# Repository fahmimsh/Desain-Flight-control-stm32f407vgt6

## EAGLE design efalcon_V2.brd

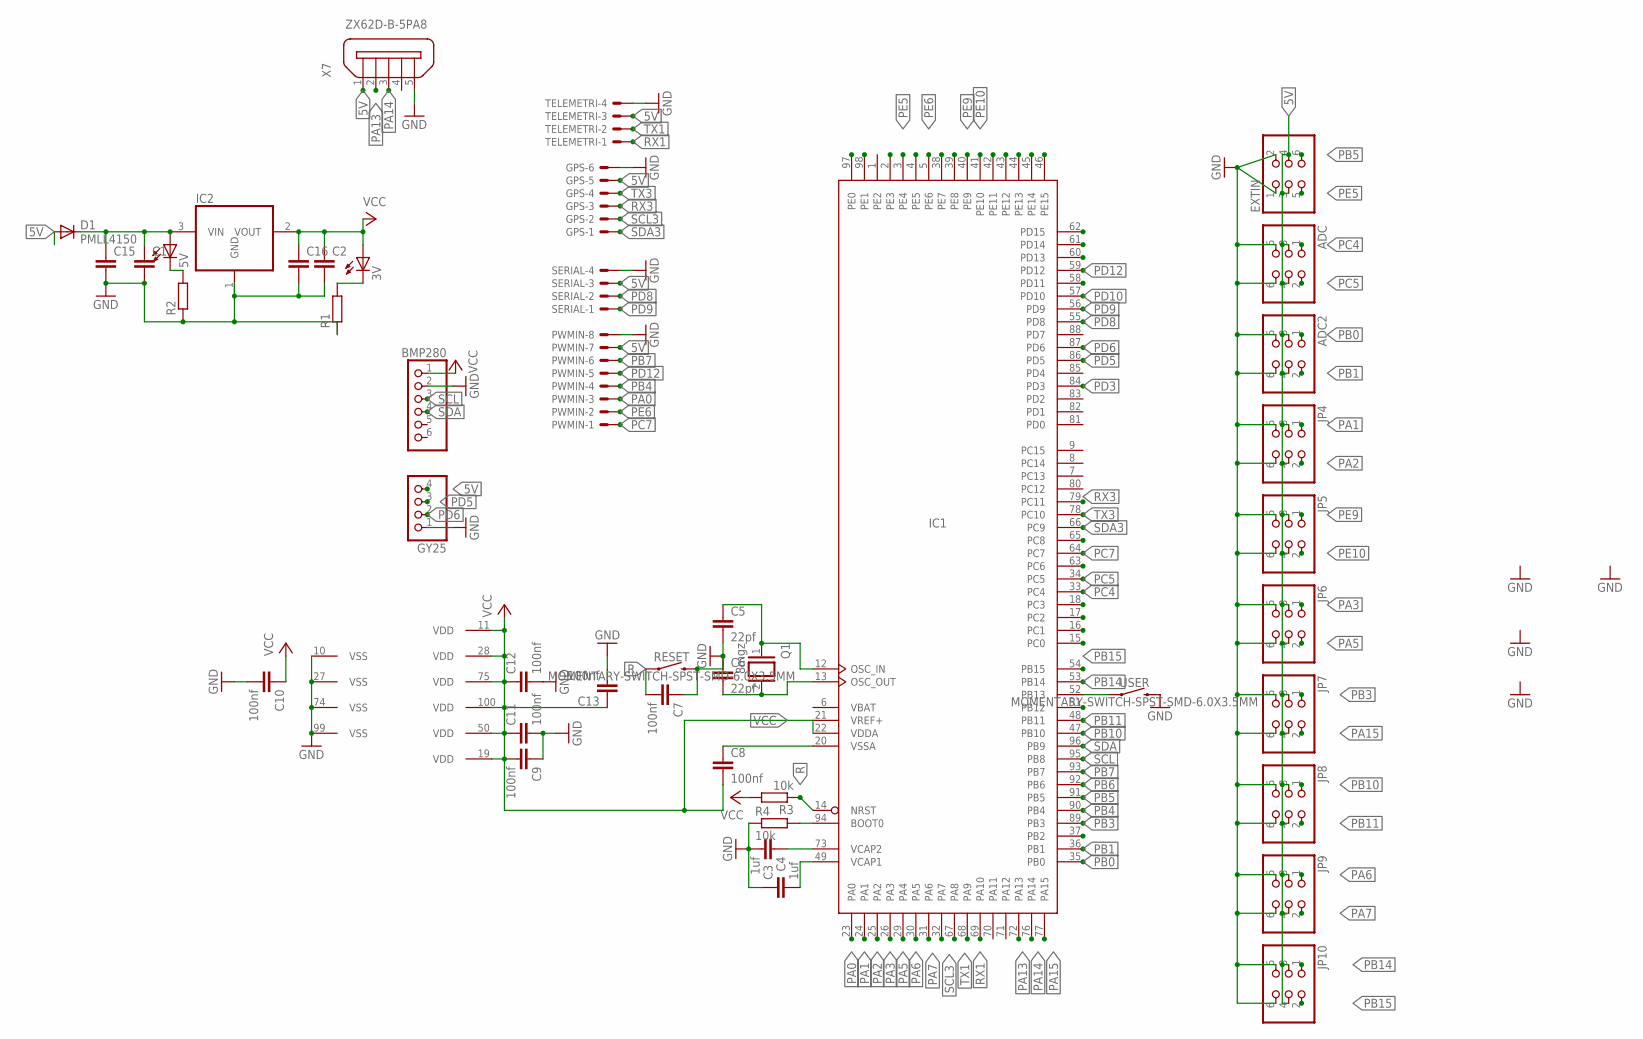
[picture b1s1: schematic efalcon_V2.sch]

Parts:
3V, 5V: LEDCHIP-LED0805; CHIP-LED0805
ADC, ADC2: PINHD-2X3; 2X03
BMP280: PINHD-1X6; 1X06
C1, C2, C15, C16: C-EUC0805; C0805
C3, C4: 1uf; C0805
C5, C6: 22pf; C0805
C7, C8, C9, C10, C11, C12, C13: 100nf; C0805
D1: PMLL4150; SOD80C
EXTIN: PINHD-2X3; 2X03
GPS: JST-XH-06-PIN-ROUND-PAD; JST-XH-06-PACKAGE-ROUND-PAD
GY25: PINHD-1X4; 1X04
IC1: STM32F407VGT; LQFP100
IC2: REG1117; SOT223
JP4, JP5, JP6, JP7, JP8, JP9, JP10: PINHD-2X3; 2X03
PWMIN: JST-XH-08-PIN-ROUND-PAD; JST-XH-08-PACKAGE-ROUND-PAD
Q1: 8mgz; QS
R1, R2: R-EU_R0805; R0805
R3, R4: 10k; R0805
RESET: MOMENTARY-SWITCH-SPST-SMD-6.0X3.5MM; TACTILE_SWITCH_SMD_6.0X3.5MM
SERIAL: JST-XH-04-PIN-ROUND-PAD; JST-XH-04-PACKAGE-ROUND-PAD
TELEMETRI: JST-XH-04-PIN-ROUND-PAD; JST-XH-04-PACKAGE-ROUND-PAD
USER: MOMENTARY-SWITCH-SPST-SMD-6.0X3.5MM; TACTILE_SWITCH_SMD_6.0X3.5MM
X7: ZX62D-B-5PA8

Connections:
5V: ADC.3, ADC.4, ADC2.3, ADC2.4, D1.A, EXTIN.3, EXTIN.4, GPS.5, GY25.4, JP4.3, JP4.4, JP5.3, JP5.4, JP6.3, JP6.4, JP7.3, JP7.4, JP8.3, JP8.4, JP9.3, JP9.4, JP10.3, JP10.4, PWMIN.7, SERIAL.3, TELEMETRI.3, X7.1
GND: ADC.5, ADC.6, ADC2.5, ADC2.6, BMP280.2, C1.2, C2.2, C3.1, C4.2, C5.2, C6.1, C7.1, C9.1, C10.2, C11.2, C12.2, C13.2, C15.2, C16.2, EXTIN.1, EXTIN.2, GPS.6, GY25.1, IC1.10 (VSS), IC1.27 (VSS), IC1.74 (VSS), IC1.99 (VSS), IC2.1 (GND), JP4.5, JP4.6, JP5.5, JP5.6, JP6.5, JP6.6, JP7.5, JP7.6, JP8.5, JP8.6, JP9.5, JP9.6, JP10.5, JP10.6, PWMIN.8, R1.1, R2.1, R4.1, RESET.2, SERIAL.4, TELEMETRI.4, USER.2, X7.5
unnamed: 5V.A, C1.1, C15.1, D1.C, IC2.3 (VIN)
unnamed: C3.2, IC1.49 (VCAP1)
unnamed: 5V.C, R2.2
unnamed: 3V.C, R1.2
unnamed: C4.1, IC1.73 (VCAP2)
unnamed: IC1.94 (BOOT0), R4.2
unnamed: C5.1, IC1.12 (OSC_IN), Q1.1
unnamed: C6.2, IC1.13 (OSC_OUT), Q1.2
unnamed: C8.1, IC1.20 (VSSA)
unnamed: IC1.52 (PB13), USER.1
PA0: IC1.23 (PA0), PWMIN.3
PA1: IC1.24 (PA1), JP4.1
PA2: IC1.25 (PA2), JP4.2
PA3: IC1.26 (PA3), JP6.1
PA5: IC1.30 (PA5), JP6.2
PA6: IC1.31 (PA6), JP9.1
PA7: IC1.32 (PA7), JP9.2
PA13: IC1.72 (PA13), X7.2
PA14: IC1.76 (PA14), X7.3
PA15: IC1.77 (PA15), JP7.2
PB0: ADC2.1, IC1.35 (PB0)
PB1: ADC2.2, IC1.36 (PB1)
PB3: IC1.89 (PB3), JP7.1
PB4: IC1.90 (PB4), PWMIN.4
PB5: EXTIN.6, IC1.91 (PB5)
PB6: IC1.92 (PB6)
PB7: IC1.93 (PB7), PWMIN.6
PB10: IC1.47 (PB10), JP8.1
PB11: IC1.48 (PB11), JP8.2
PB14: IC1.53 (PB14), JP10.1
PB15: IC1.54 (PB15), JP10.2
PC4: ADC.1, IC1.33 (PC4)
PC5: ADC.2, IC1.34 (PC5)
PC7: IC1.64 (PC7), PWMIN.1
PD3: IC1.84 (PD3)
PD5: GY25.3, IC1.86 (PD5)
PD6: GY25.2, IC1.87 (PD6)
PD8: IC1.55 (PD8), SERIAL.2
PD9: IC1.56 (PD9), SERIAL.1
PD10: IC1.57 (PD10)
PD12: IC1.59 (PD12), PWMIN.5
PE5: EXTIN.5, IC1.4 (PE5)
PE6: IC1.5 (PE6), PWMIN.2
PE9: IC1.40 (PE9), JP5.1
PE10: IC1.41 (PE10), JP5.2
R: C7.2, IC1.14 (NRST), R3.1, RESET.1
RX1: IC1.69 (PA10), TELEMETRI.1
RX3: GPS.3, IC1.79 (PC11)
SCL: BMP280.3, IC1.95 (PB8)
SCL3: GPS.2, IC1.67 (PA8)
SDA: BMP280.4, IC1.96 (PB9)
SDA3: GPS.1, IC1.66 (PC9)
TX1: IC1.68 (PA9), TELEMETRI.2
TX3: GPS.4, IC1.78 (PC10)
VBAT: IC1.6 (VBAT)
VCC: 3V.A, BMP280.1, C2.1, C8.2, C9.2, C10.1, C11.1, C12.1, C13.1, C16.1, IC1.11 (VDD), IC1.19 (VDD), IC1.21 (VREF+), IC1.22 (VDDA), IC1.28 (VDD), IC1.50 (VDD), IC1.75 (VDD), IC1.100 (VDD), IC2.2 (VOUT), R3.2

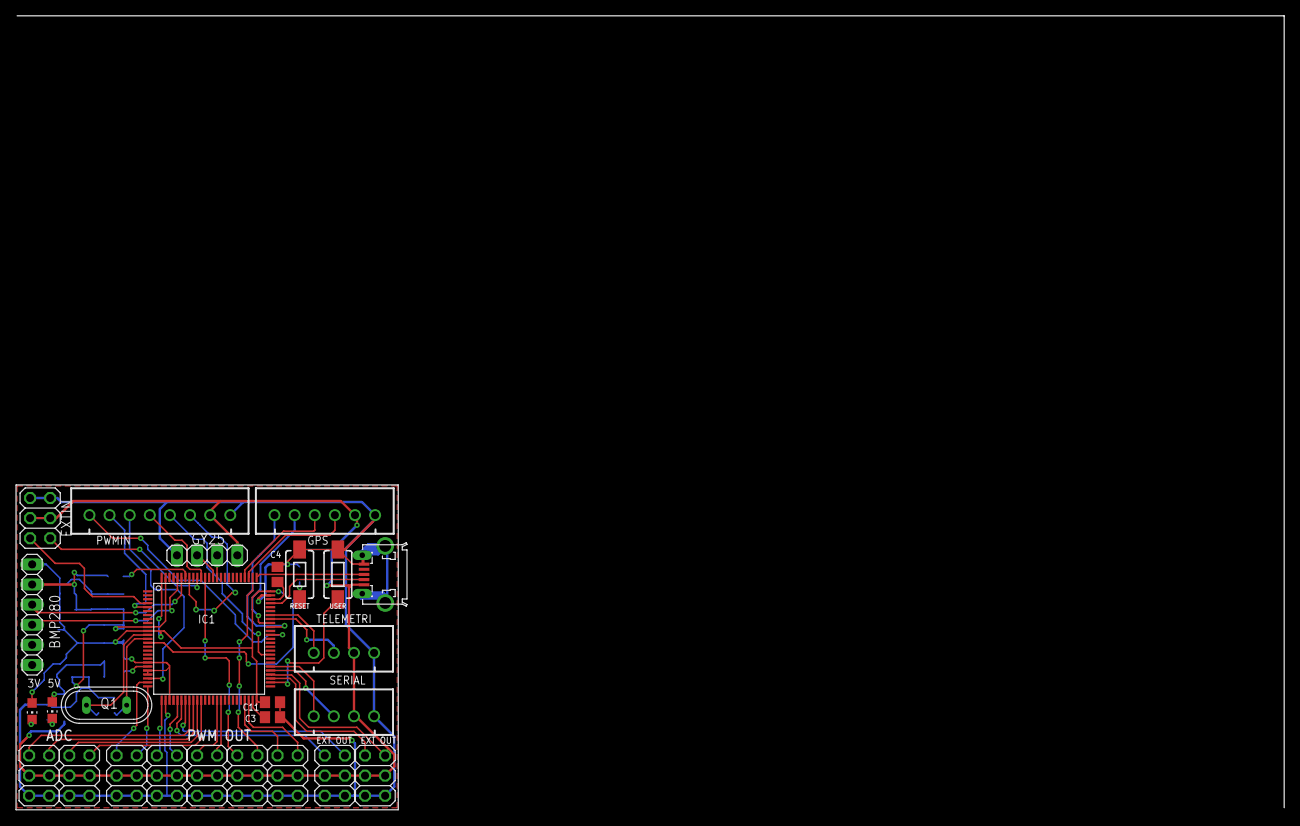
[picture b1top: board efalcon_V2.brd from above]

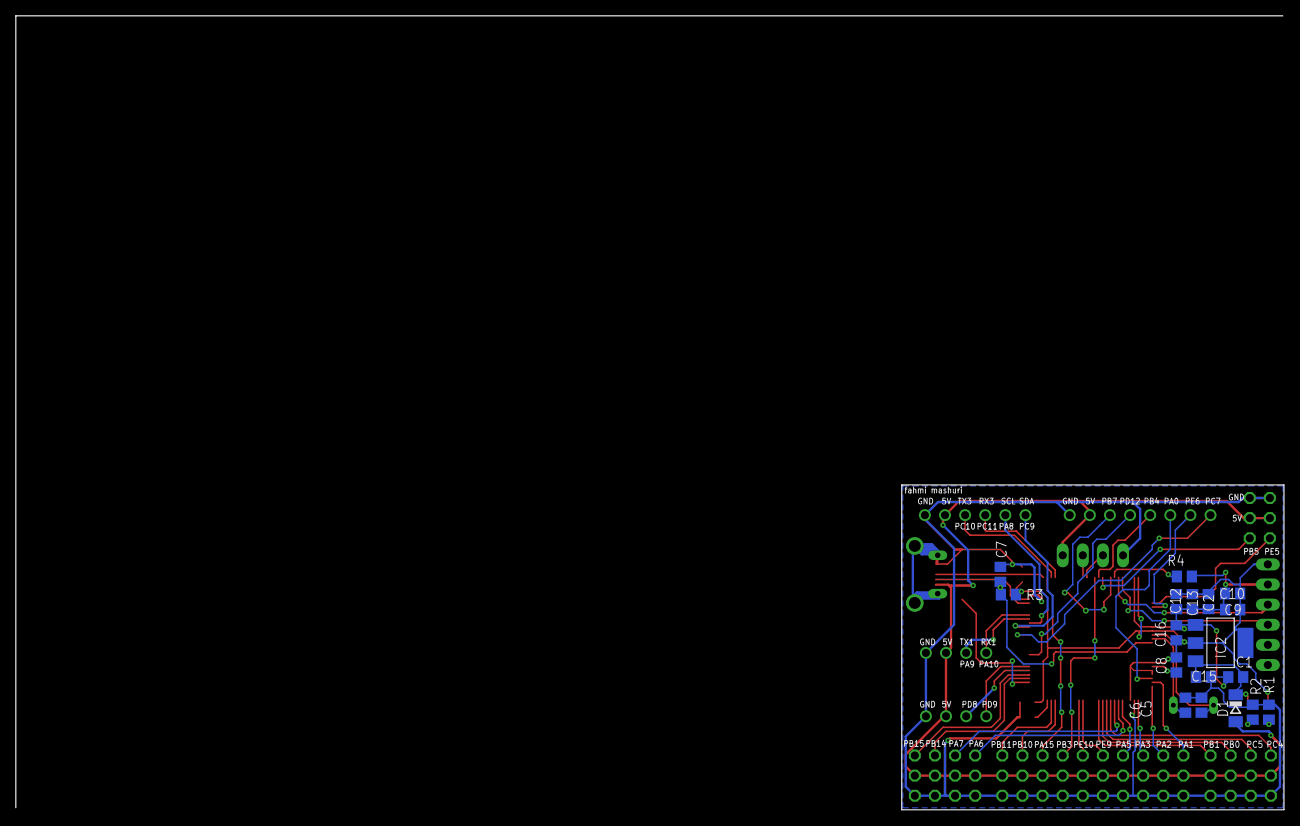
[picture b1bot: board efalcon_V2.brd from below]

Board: 2 copper layers, 160.1 x 100.2 mm, 44 parts (18 on the bottom side), 54 nets.

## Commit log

2020-09-29 unggahdesain

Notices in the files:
parts and their libraries:
SparkFun-Switches: Licensing: Creative Commons ShareAlike 4.0 International - https://creativecommons.org/licenses/by-sa/4.0
